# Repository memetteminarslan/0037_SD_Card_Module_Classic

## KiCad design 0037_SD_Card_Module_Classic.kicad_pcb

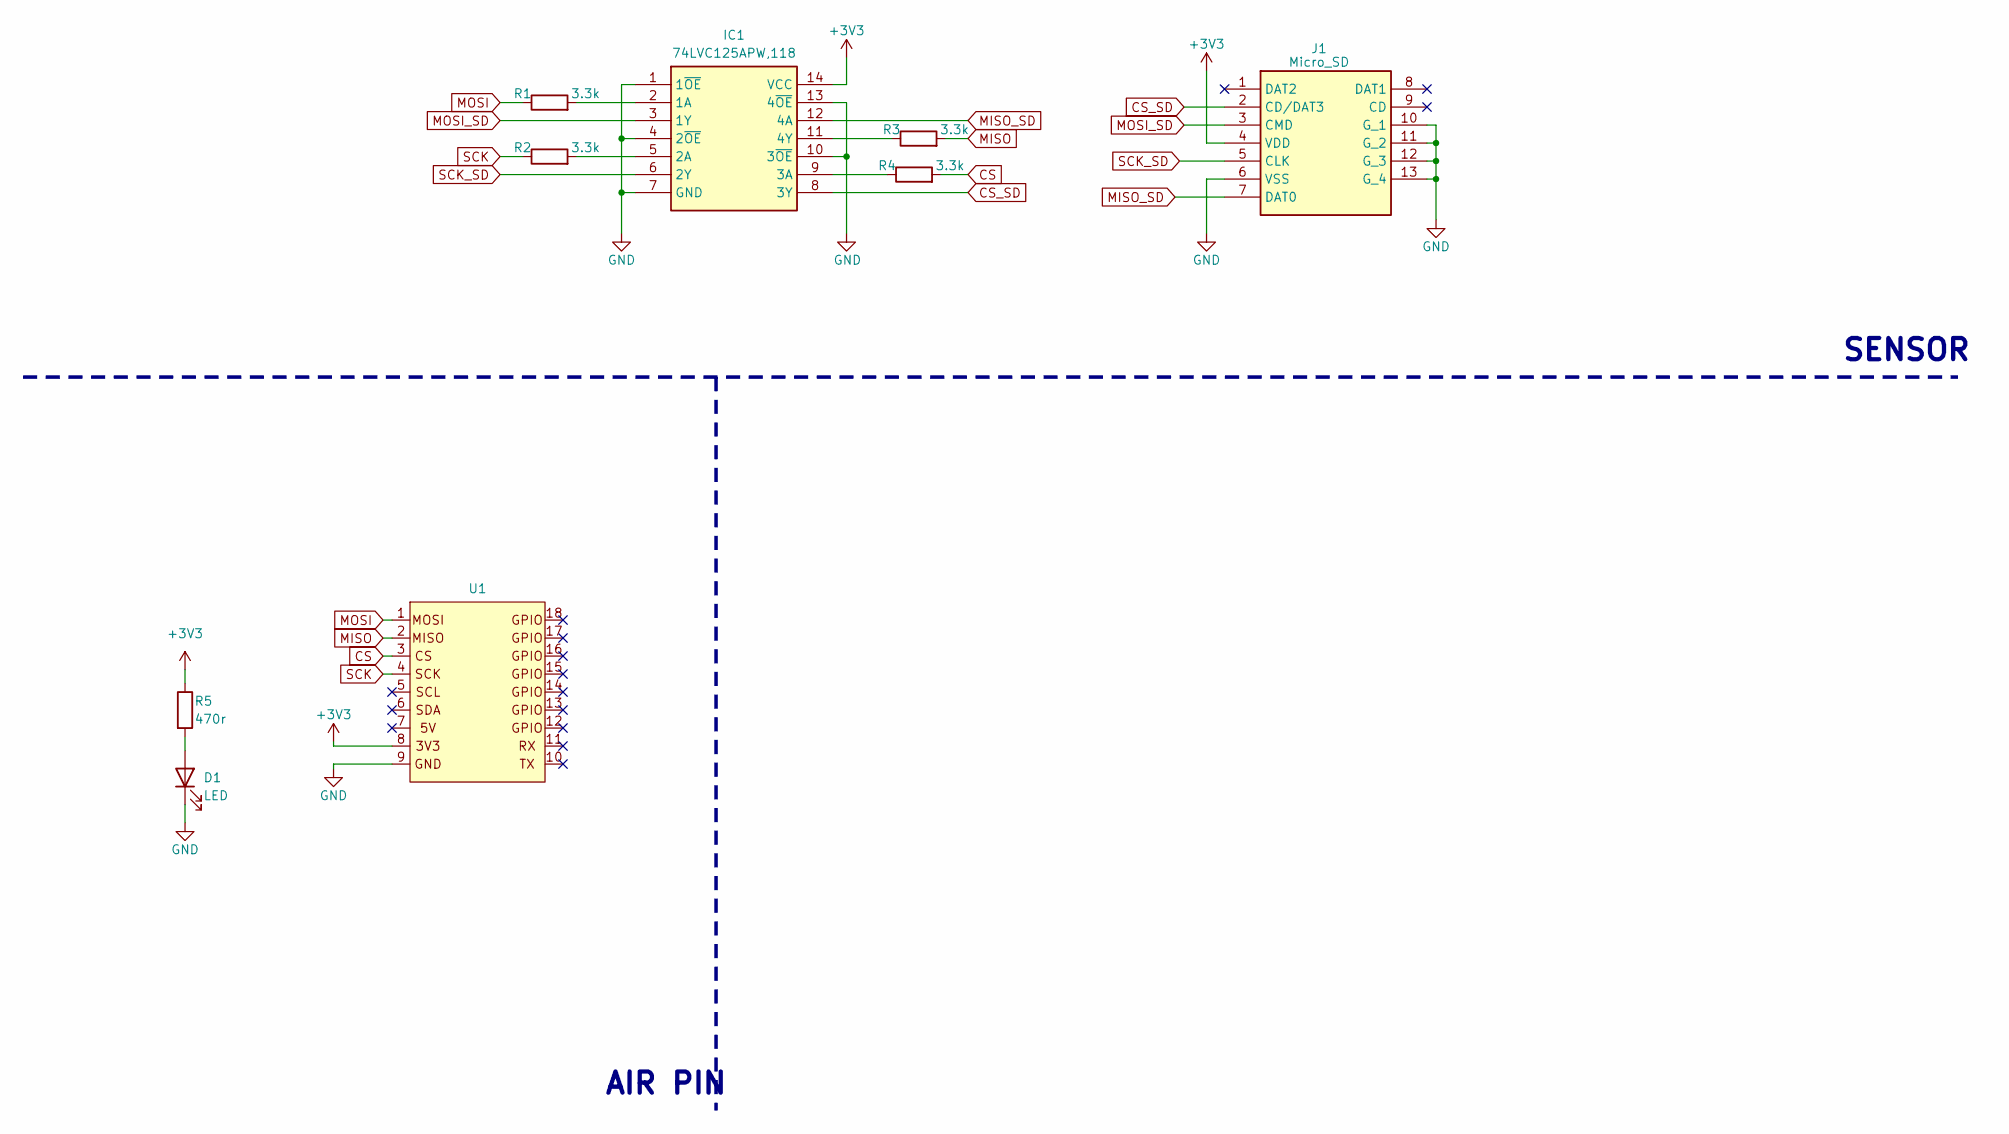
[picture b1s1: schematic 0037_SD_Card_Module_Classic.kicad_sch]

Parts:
D1: LED; LED_0603_1608Metric
IC1: 74LVC125APW,118; SOP65P640X110-14N; Mouser Part Number 771-74LVC125APW-T
J1: Micro_SD; L-KLS1-TF-003-H1.85-R; Manufacturer_Part_Number L-KLS1-TF-003-H1.85-R
R1, R2, R3, R4: 3.3k; R_0603_1608Metric
R5: 470r; R_0603_1608Metric
U1: pin_header

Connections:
+3V3: IC1.14 (VCC), J1.4 (VDD), R5.1, U1.8
CS: R4.2, U1.3
CS_SD: IC1.8 (3Y), J1.2 (CD/DAT3)
GND: D1.1 (K), IC1.1 (1~OE), IC1.4 (2~OE), IC1.7 (GND), IC1.10 (3~OE), IC1.13 (4~OE), J1.6 (VSS), J1.10 (G_1), J1.11 (G_2), J1.12 (G_3), J1.13 (G_4), U1.9
MISO: R3.2, U1.2
MISO_SD: IC1.12 (4A), J1.7 (DAT0)
MOSI: R1.1, U1.1
MOSI_SD: IC1.3 (1Y), J1.3 (CMD)
unnamed: D1.2 (A), R5.2
unnamed: IC1.2 (1A), R1.2
unnamed: IC1.5 (2A), R2.2
unnamed: IC1.9 (3A), R4.1
unnamed: IC1.11 (4Y), R3.1
SCK: R2.1, U1.4
SCK_SD: IC1.6 (2Y), J1.5 (CLK)

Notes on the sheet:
SENSOR
AIR PIN

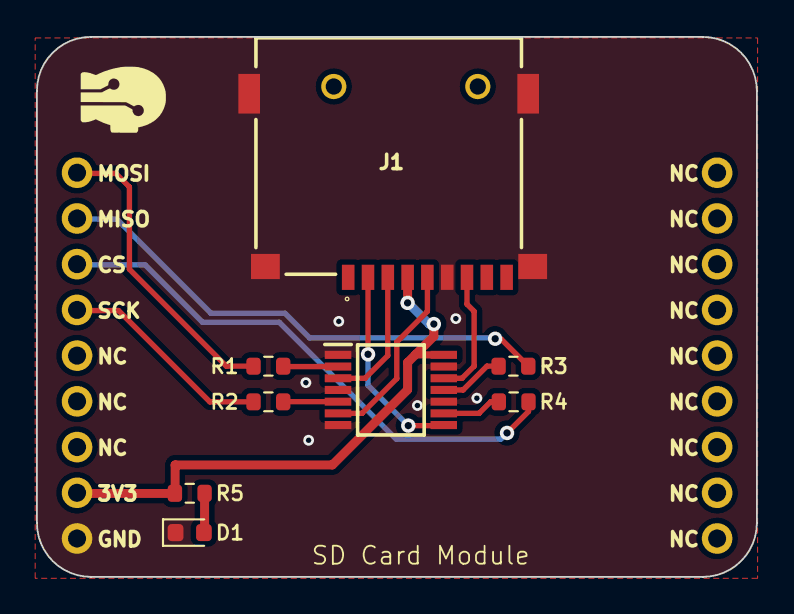
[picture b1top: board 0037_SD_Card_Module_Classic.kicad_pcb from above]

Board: 2 copper layers, 40.0 x 30.0 mm, 9 parts (0 on the bottom side), 15 nets.
